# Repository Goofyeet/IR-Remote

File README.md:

# IR-Remote

In this project I wrote some AVR assembly code for an ATTiny 12V microcontroller to control a tower fan. I used an oscilloscope to reverse engineer the original remotes signals.

Check out the remote in action in the media folder!

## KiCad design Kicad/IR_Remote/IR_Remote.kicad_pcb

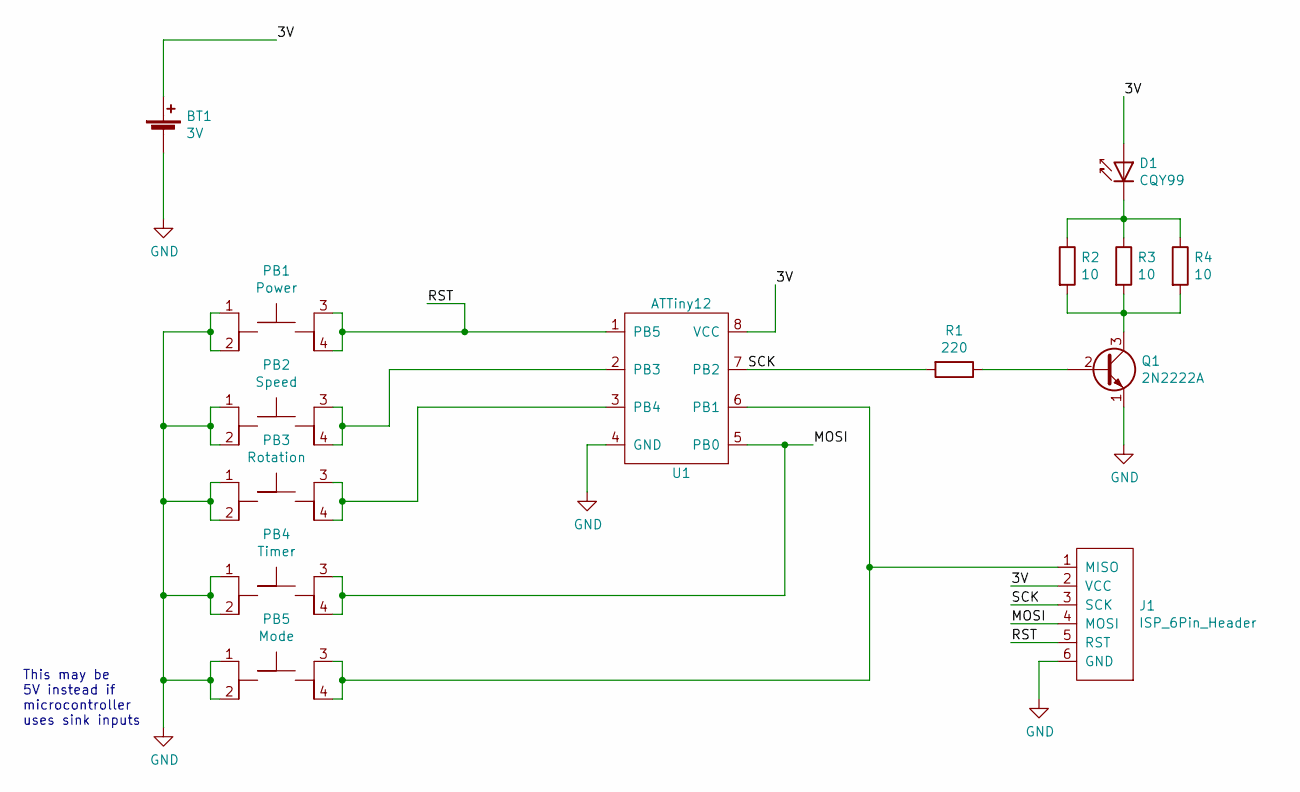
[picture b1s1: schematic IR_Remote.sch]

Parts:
BT1: 3V; CR2032_BH-124A-1
D1: CQY99; LED_D5.0mm_Horizontal_O1.27mm_Z3.0mm_IRGrey
J1: ISP_6Pin_Header; 2X3_ICSP_Header
PB1: Power; Switch_Tactile_THT_6x6mm
PB2: Speed; Switch_Tactile_THT_6x6mm
PB3: Rotation; Switch_Tactile_THT_6x6mm
PB4: Timer; Switch_Tactile_THT_6x6mm
PB5: Mode; Switch_Tactile_THT_6x6mm
Q1: 2N2222A; TO-92-3
R1: 220; R_Axial_DIN0207_L6.3mm_D2.5mm_P7.62mm_Horizontal
R2, R3, R4: 10; R_Axial_DIN0207_L6.3mm_D2.5mm_P7.62mm_Horizontal
U1: ATTiny12

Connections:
/3V: BT1.1 (+), D1.2 (A), J1.2 (VCC), U1.8 (VCC)
/MOSI: J1.4 (MOSI), PB4.3, PB4.4, U1.5 (PB0)
/RST: J1.5 (RST), PB1.3, PB1.4, U1.1 (PB5)
/SCK: J1.3 (SCK), R1.2, U1.7 (PB2)
GND: BT1.2 (-), J1.6 (GND), PB1.1, PB1.2, PB2.1, PB2.2, PB3.1, PB3.2, PB4.1, PB4.2, PB5.1, PB5.2, Q1.1 (E), U1.4 (GND)
unnamed: D1.1 (K), R2.1, R3.1, R4.1
unnamed: J1.1 (MISO), PB5.3, PB5.4, U1.6 (PB1)
unnamed: PB2.3, PB2.4, U1.2 (PB3)
unnamed: PB3.3, PB3.4, U1.3 (PB4)
unnamed: Q1.2 (B), R1.1
unnamed: Q1.3 (C), R2.2, R3.2, R4.2

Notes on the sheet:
This may be 5V instead if microcontroller uses sink inputs

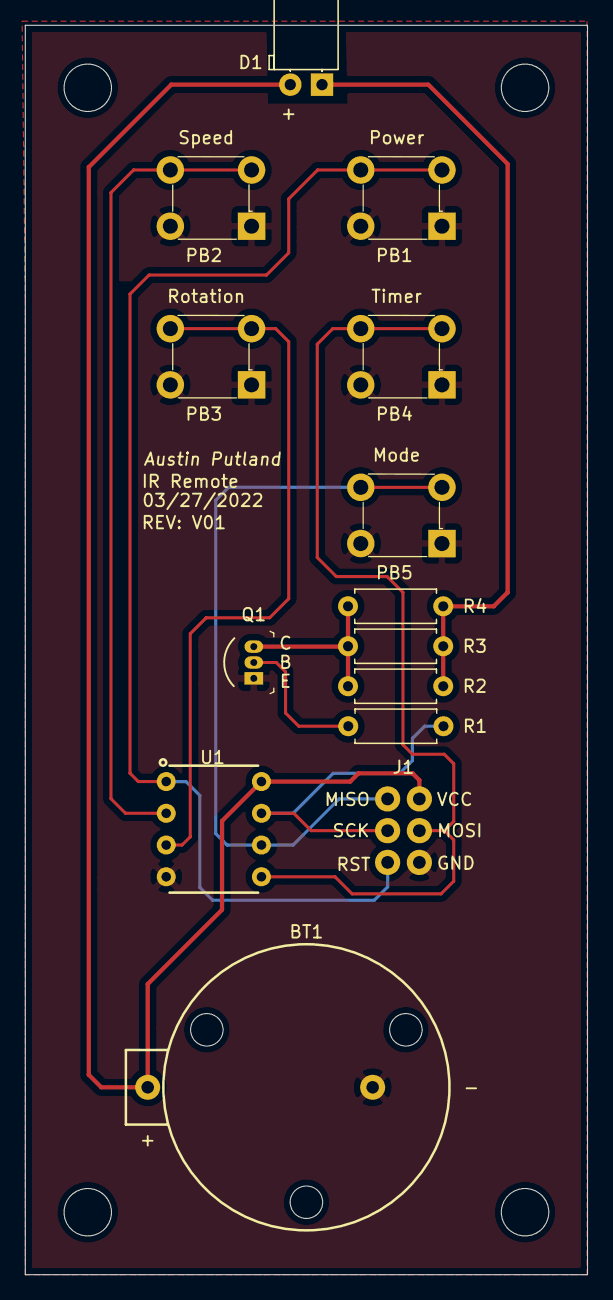
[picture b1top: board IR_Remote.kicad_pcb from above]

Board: 2 copper layers, 45.0 x 100.0 mm, 14 parts (0 on the bottom side), 11 nets.

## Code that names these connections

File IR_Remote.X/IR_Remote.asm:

#define DEBUG 1
      
;global registers    
    
.def	    temp =r16	;general temporary register	  

;signal codes
    
.equ	    PreambleH =0xfe
.equ	    PreambleL =0x01
.equ	    PowerH =0xfc
.equ	    PowerL =0x03
.equ	    SpeedH =0xf8    
.equ	    SpeedL =0x07    
.equ	    RotateH =0xec   
.equ	    RotateL =0x13    
.equ	    TimerH =0xf4    
.equ	    TimerL =0x0b    
.equ	    ModeH =0xf0    
.equ	    ModeL =0x0f  
    
;Pushbutton pins
    
#if DEBUG
.equ	    normal =0x1b 
.equ	    SpeedPB =0x13	;PB3
.equ	    RotatePB =0x0b   	;PB4
.equ	    TimerPB =0x1a	;PB0
.equ	    ModePB =0x19	;PB1 
    
#else
.equ	    normal =0x3b
.equ	    PowerPB =0x1b	;PB5 
.equ	    SpeedPB =0x33	;PB3
.equ	    RotatePB =0x2b	;PB4
.equ	    TimerPB =0x3a	;PB0
.equ	    ModePB =0x39	;PB1   
#endif
    
;delays
.equ	    finemark =61
.equ	    finezerospace =192	
.equ	    fineonespace =79	
.equ	    mediummark =1
.equ	    mediumonespace =7	
.equ	    mediumzerospace =1	   
.equ	    finestart =199
.equ	    mediumstart =5
.equ	    fstartdelay =245  
.equ	    mstartdelay =6
.equ	    fBounceDelay =250
.equ	    mBounceDelay =12
    
;toggle
.equ	    togglebit =0b00000100

;toggle register
.def	    invertedbit =r8

;scan routine registers
.def	    fineBounce =r9
.def	    medBounce =r10
.def	    status =r11
.def	    pinscans =r17
.def	    pinstatus =r18 
    
;output routine
.def	    fencodeloop =r12
.def	    medencodeloop =r13        
.def	    encoderbyte =r14    
.def	    encoderbyteH =r15     
.def	    signalH =r19
.def	    signalL =r20 
    
;delay routine
.def	    fine =r22
.def	    medium =r23
.def	    finedelay =r24
.def	    mediumdelay =r25
;r26 used for signal loop counter
;r27 used for toggleoutput macro
    
    
;macro
.macro	    toggleoutput    ;toggles output pin
    in @0,PORTB		    ;@0: invertedbit
    ldi @1,@2		    ;@1: r27
    eor @0,@1		    ;@2: togglebit
    out PORTB,@0    
.endmacro    
    
    
;########Interrupt Vectors##############
.org 0    
    rjmp    reset	;reset vector
.org 2
    rjmp    scan	;pin change interrupt vector 
    
    
    
;#######################################################################
;			    MAIN routine
;#######################################################################
    
reset:
    ldi temp,0x20
    out GIMSK,temp	;only enables pin change interrupt
    ldi temp,0x04
    out DDRB,temp	;PB2 is only output    
    ldi temp,0x1b	;stores bit mask for enabling input pull-ups
    out	PORTB,temp	;enables input pull-ups
    sbi ACSR,7		;Disables analog comparator
       
    rcall debounceDelay
    
main:
    ldi temp,0x30
    out MCUCR,temp	;enable sleep mode   
    sei			;enable global interrupts
    sleep		;Tells Microcontroller to enter sleep mode
    rjmp main		;loop over sleep instruction
    
 
/*
#######################################################################
		    pin change interrupt routine
#######################################################################
*/
    
scan:
    in status,SREG	    ;preserve status register
    ser pinscans	    ;set pinscans to 255
    
rcall debounceDelay
	   
scan1:    
    in pinstatus,PINB	    ;store PINB register values in pinstatus
    
#if !DEBUG
    cpi pinstatus,PowerPB   ;if only power pb is pushed
    breq sendPower	    ;branch to sendPower
#endif  
 
    cpi pinstatus,SpeedPB   ;if only speed pb is pushed
    breq sendSpeed	    ;branch to sendSpeed
    
    cpi pinstatus,RotatePB   ;if only rotate pb is pushed
    breq sendRotate	     ;branch to sendRotate
    
    cpi pinstatus,TimerPB   ;if only timer pb is pushed
    breq sendTimer	    ;branch to sendTimer
    
    cpi pinstatus,ModePB    ;if only mode pb is pushed
    breq sendMode	    ;branch to sendMode
    
    rjmp exit		    ;jump to exit interrupt
    
sendPower:
    ldi signalH,PowerH
    ldi signalL,PowerL
    rcall output
    rjmp exit
     
sendSpeed:
    ldi signalH,SpeedH
    ldi signalL,SpeedL
    rcall output
    rjmp exit
    
sendRotate:
    ldi signalH,RotateH
    ldi signalL,RotateL   
    rcall output
    rjmp exit
    
sendTimer:
    ldi signalH,TimerH
    ldi signalL,TimerL
    rcall output
    rjmp exit
    
sendMode:
    ldi signalH,ModeH
    ldi signalL,ModeL   
    rcall output
    
exit:
    in pinstatus,PINB
    cpi pinstatus,normal
    breq returnInterrupt    
    rjmp exit
    
returnInterrupt:
    out SREG,status	;restore status register 
    reti
    
;*****end of pin scan********************************
    

;****************************************************
;		Debounce Delay
;****************************************************
debounceDelay:
    ldi temp,mBounceDelay
    mov medBounce,temp    
    ldi temp,fBounceDelay
    mov fineBounce,temp
    mbounce:
	    mov fineBounce,temp
    fbounce:
	    dec fineBounce
	    nop
	    brne fbounce
	    dec medBounce
	    brne mbounce
	    ret
	    
;**************************************************

	    
;********************************************    
;	Output, creates output signal    
;********************************************    
Output:

start:
;9ms high pulse followed by a 4.5ms low pulse
    ldi fine,finestart
    ldi medium,mediumstart
    rcall modulator
    ldi finedelay,fstartdelay
    ldi mediumdelay,mstartdelay
    rcall delay
    
preamble:
;send Preamble: 0xfe01  
    ldi temp,preambleH
    mov encoderbyteH,temp
    ldi temp,preambleL
    mov encoderbyte,temp
    rcall encoder_init
      
;loop 2 times 
    ldi r26,2
code:    
    mov encoderbyteH,signalH
    mov encoderbyte,signalL
    rcall encoder_init
    dec r26
    brne code
    
;send stop bit
stop:
    ldi fine,finemark
    ldi medium,mediummark
    rcall modulator
    ret
    

;******encoder, encodes each bit of signal*************    
mediumencode:
    ldi temp,8
    mov fencodeloop,temp
    mov encoderbyte,encoderbyteH
    rjmp encoder
    
encoder_init:
    ldi temp,8
    mov fencodeloop,temp
    ldi temp,2
    mov medencodeloop,temp    
    
encoder:
    ror encoderbyte    ;shifts right bit into carry
    
    ldi medium,mediummark
    ldi fine,finemark
    rcall modulator
   
    brcs highbit
    
lowBit:
//if carry is 0
    ldi finedelay,finezerospace
    ldi mediumdelay,mediumzerospace
    rcall delay
    rjmp handleloop
     
highBit:
    ldi finedelay,fineonespace
    ldi mediumdelay,mediumonespace
    rcall delay

    
handleloop:
    dec fencodeloop
    brne encoder
    dec medencodeloop
    brne mediumencode
    ret
      
;delay for low pulse
delay:
    mov temp,finedelay
    mediumloop:
    mov finedelay,temp
    fineloop:
    dec finedelay
    brne fineloop
    dec mediumdelay
    brne mediumloop
    ret
    
;************************************************
;	Modulator, modulates high bits/pulses   
;************************************************
modulator:
    mov temp,fine				;store fine value
    
magain:	  mov fine,temp
    
fagain:   
    toggleoutput invertedbit,r27,togglebit	;toggle output macro
    nop
    nop 
    dec fine
    brne fagain
    dec medium
    brne magain
    ldi temp,0b00011011				;turn off output
    out PORTB,temp
    ret
    
;******end of modulator********************************

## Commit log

2022-05-08 added Kicad folder
2022-05-08 added IR Remote Mplab X project, assembly code
2022-05-08 added register values spreadsheet
2022-05-08 added Pseudocode doc
2022-05-08 restore code back to semi-working condition
2022-05-16 added code to debug quickly using entirely lvsp
2022-05-16 updated cmd options file and debug build
2022-05-17 deleted carrierloop line that was commented out
2022-05-23 added git ignore file
2022-05-23 added AVRdude options text file
2022-05-23 add Pseudocode file
2022-05-23 add register values spreadsheet
2022-05-23 add assembly code file
2022-05-23 added HVSP fuse reset file
2022-05-23 add IR Remote questions file
2022-05-23 added arduino IR receive and send code
2022-05-24 enables sleep mode before interrupt enable, fixes interrupt on powerup
2022-05-24 added debounce delay
2023-02-08 Add media files
